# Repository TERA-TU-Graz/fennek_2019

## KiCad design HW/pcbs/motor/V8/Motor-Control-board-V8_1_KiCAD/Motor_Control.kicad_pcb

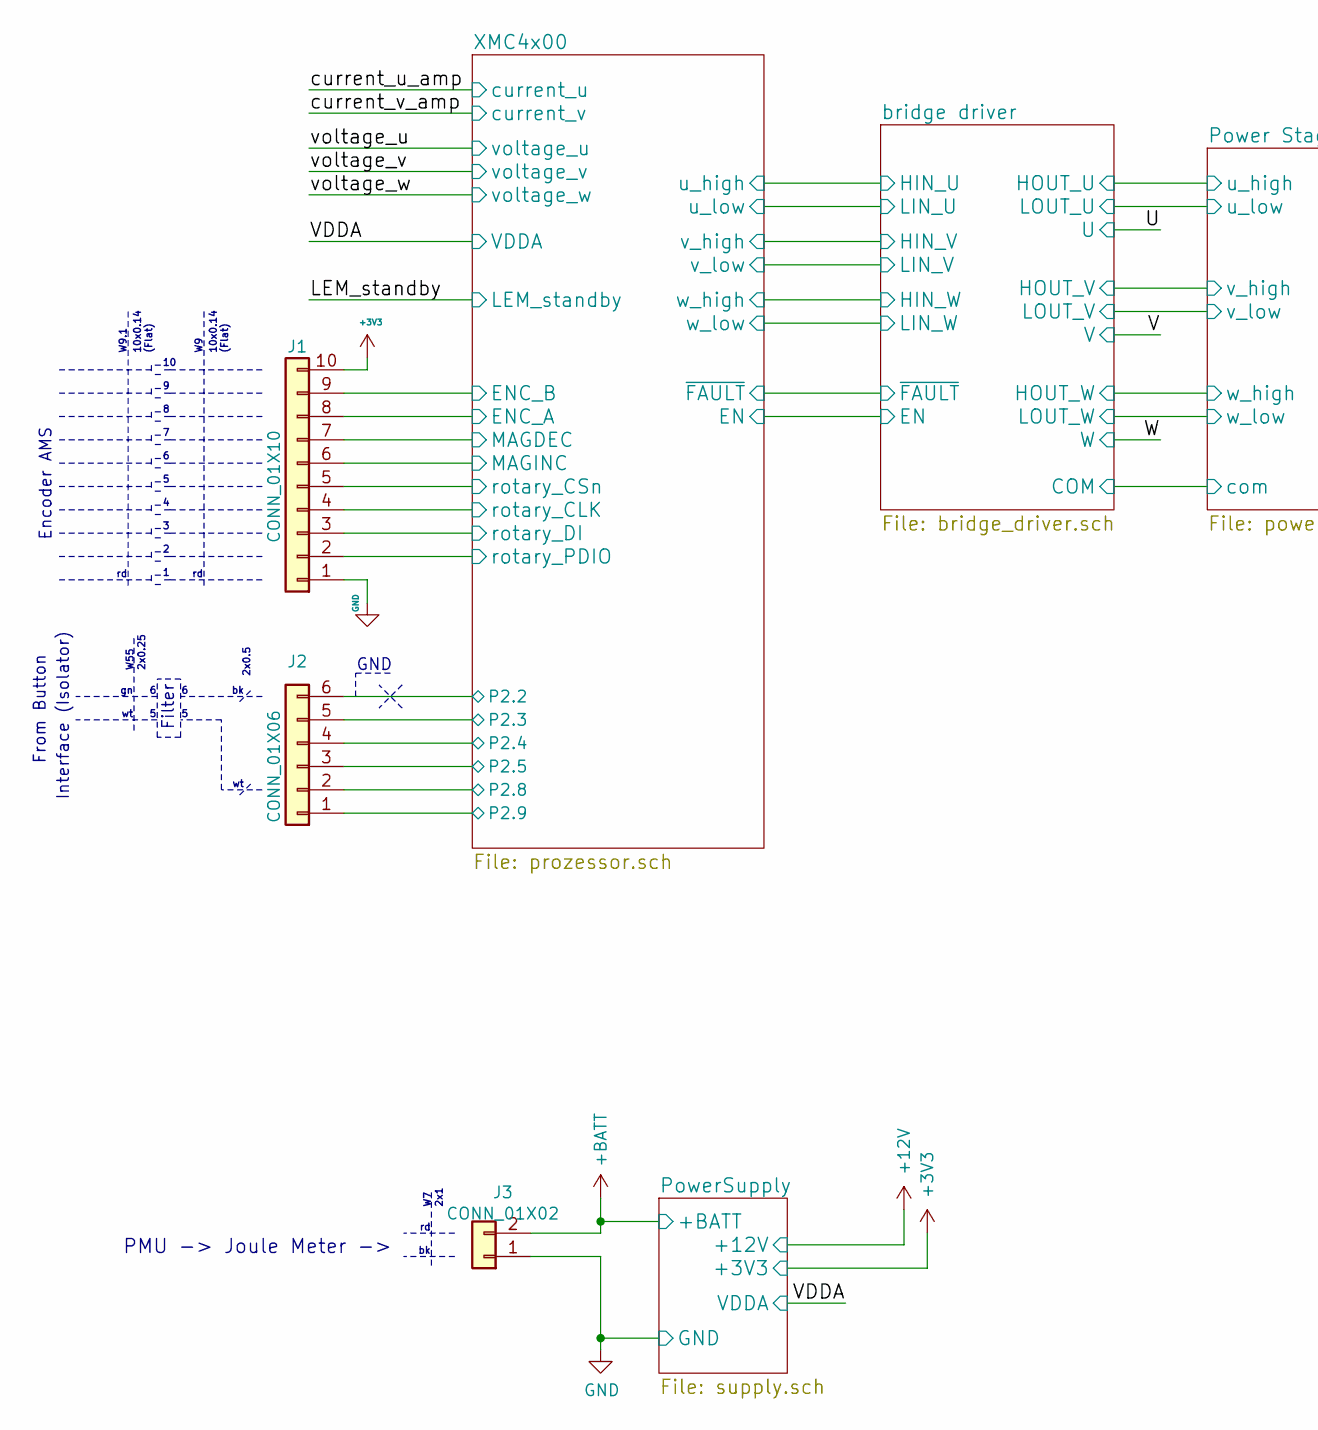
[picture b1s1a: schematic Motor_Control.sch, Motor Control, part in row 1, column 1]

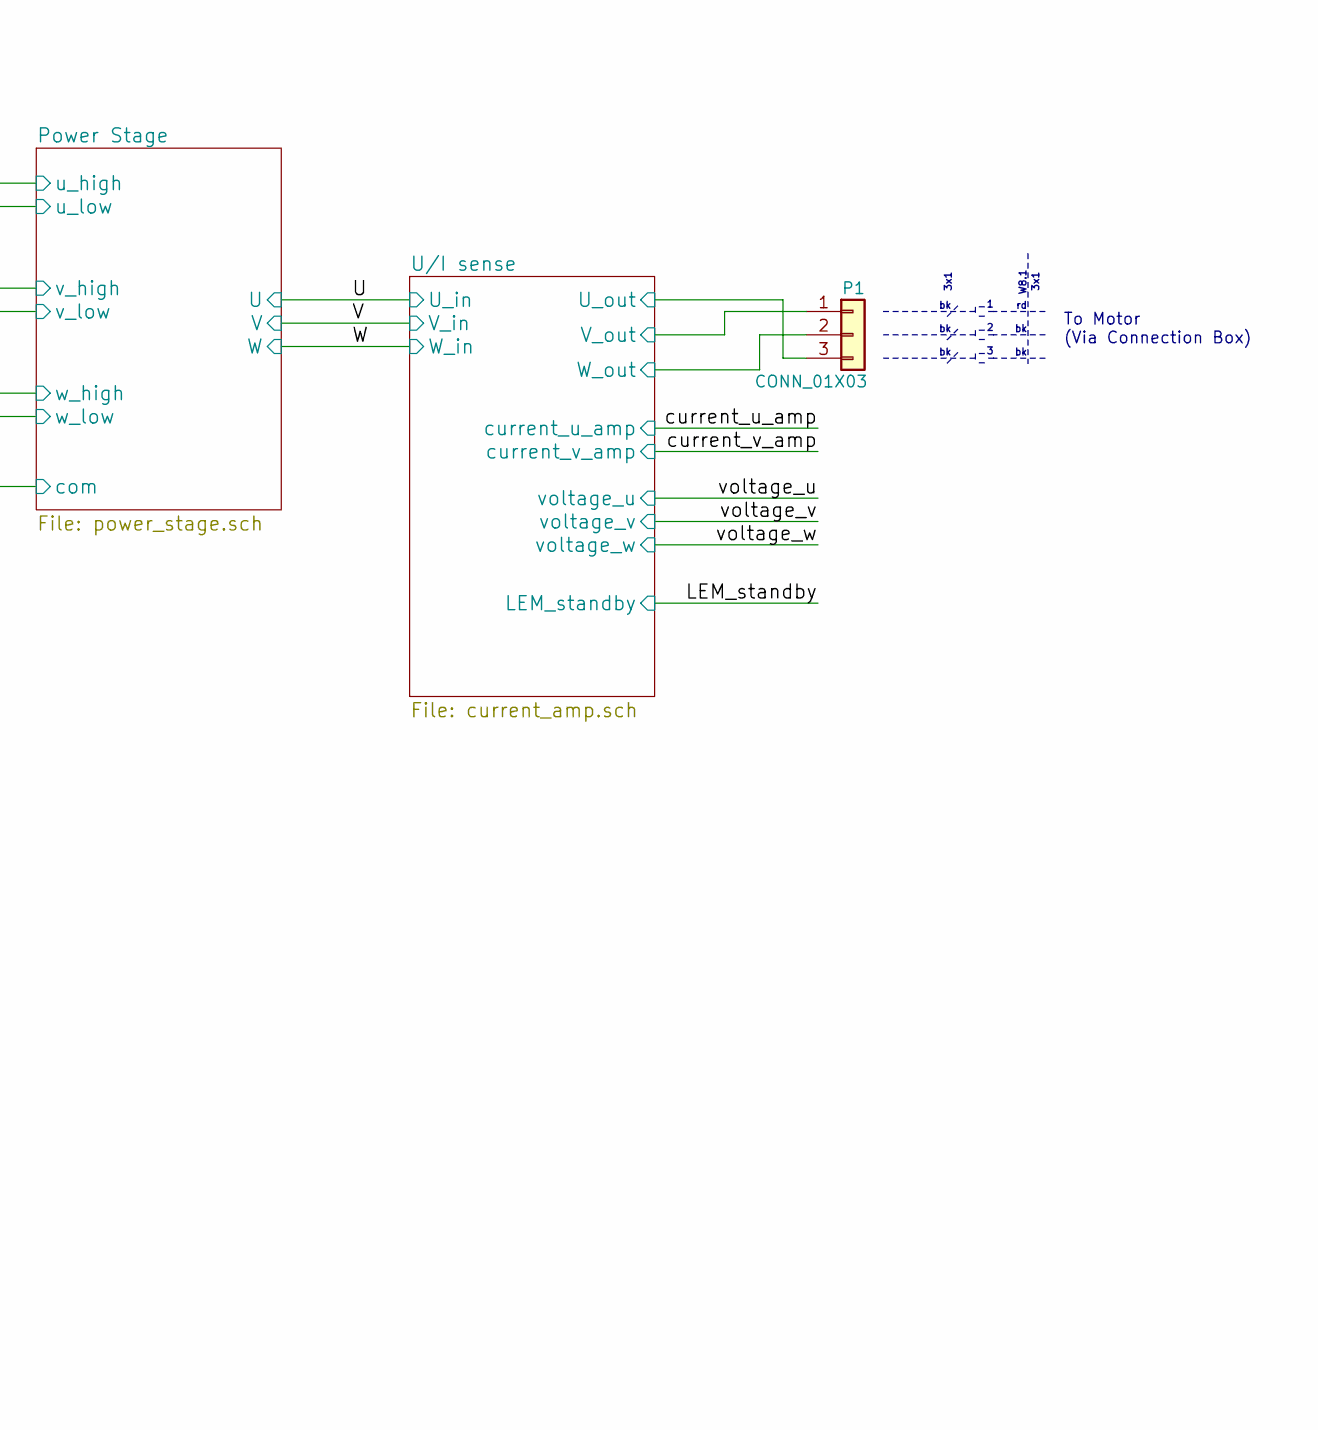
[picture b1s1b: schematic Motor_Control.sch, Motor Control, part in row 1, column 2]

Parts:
J1: CONN_01X10; Molex_PicoBlade_53398-1071_10x1.25mm_Straight
J2: CONN_01X06; Pin_Header_Straight_1x06_Pitch2.54mm
J3: CONN_01X02; PhoenixContact_MSTB-GF_02x5.08mm_Angled_ThreadedFlange
P1: CONN_01X03; PhoenixContact_MSTBA-G_03x5.08mm_Angled

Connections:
+3V3: J1.10; also elsewhere on the board
+BATT: J3.2; also elsewhere on the board
<root sheet>ENC_A: J1.8; also elsewhere on the board
<root sheet>ENC_B: J1.9; also elsewhere on the board
<root sheet>MAGDEC: J1.7; also elsewhere on the board
<root sheet>MAGINC: J1.6; also elsewhere on the board
<root sheet>U_out: P1.3; also elsewhere on the board
<root sheet>V_out: P1.1; also elsewhere on the board
<root sheet>W_out: P1.2; also elsewhere on the board
<root sheet>rotary_CLK: J1.4; also elsewhere on the board
<root sheet>rotary_CSn: J1.5; also elsewhere on the board
<root sheet>rotary_DI: J1.3; also elsewhere on the board
<root sheet>rotary_PDIO: J1.2; also elsewhere on the board
GND: J1.1, J3.1; also elsewhere on the board
unnamed 58: J2.1; also elsewhere on the board
unnamed 59: J2.2; also elsewhere on the board
unnamed 60: J2.3; also elsewhere on the board
unnamed 61: J2.4; also elsewhere on the board
unnamed 62: J2.5; also elsewhere on the board
unnamed 63: J2.6; also elsewhere on the board

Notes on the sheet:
10x0.14 (Flat)
W9.1
Encoder AMS
3x1
W8.1
To Motor (Via Connection Box)
PMU -> Joule Meter ->
2x1
GND
2x0.5
Filter
From Button
Interface (Isolator)
2x0.25
W55

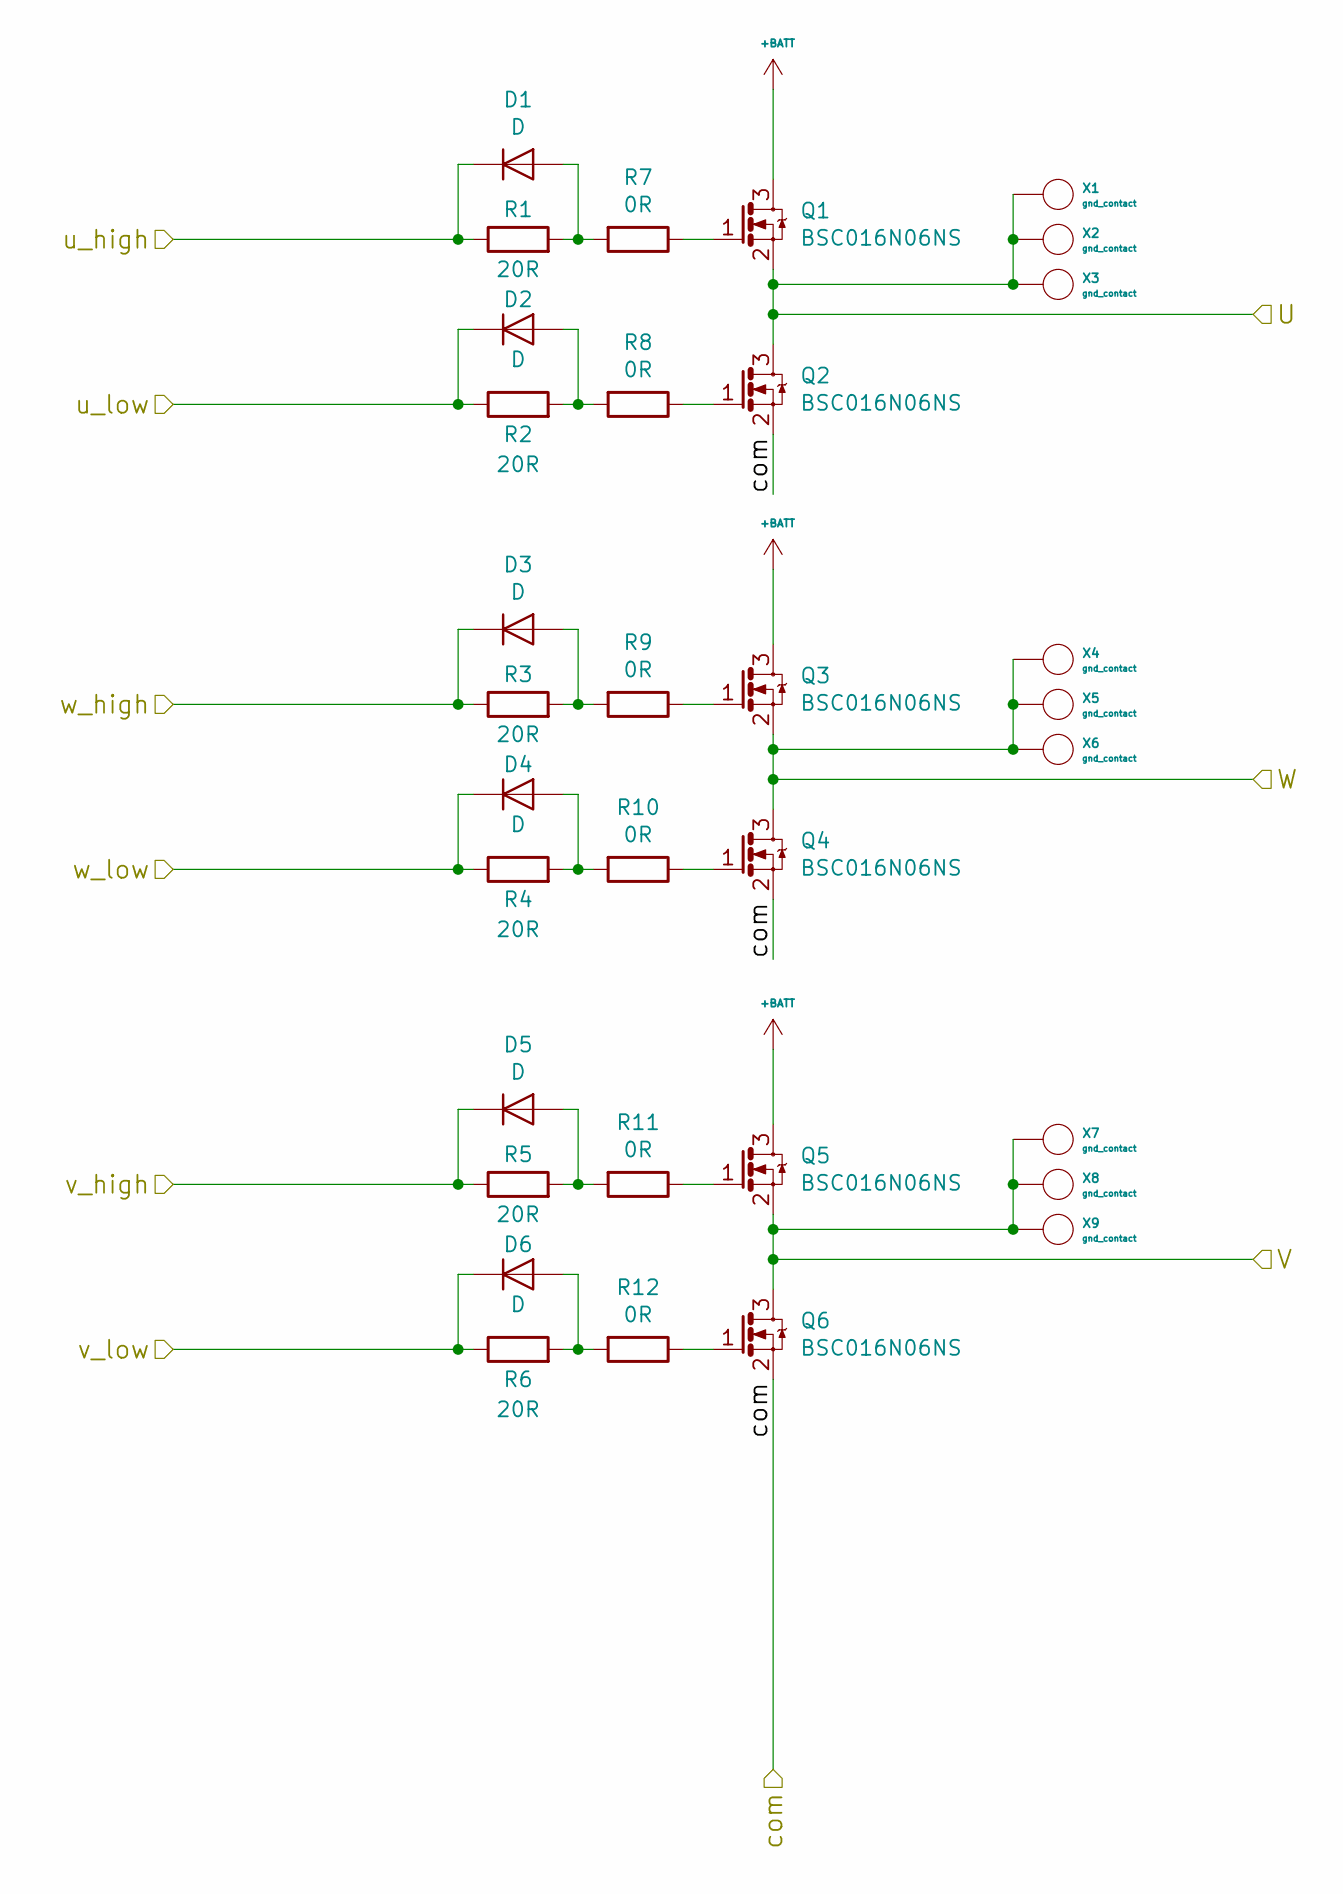
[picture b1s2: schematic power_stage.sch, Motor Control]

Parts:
D1, D2, D3, D4, D5, D6: D; SOD-323
Q1, Q2, Q3, Q4, Q5, Q6: BSC016N06NS; INF-PG-TDSON-8
R1, R2, R3, R4, R5, R6: 20R; R_0603in
R7, R8, R9, R10, R11, R12: 0R; R_0603in
X1, X2, X3, X4, X5, X6, X7, X8, X9: gnd_contact; via_0.4mm

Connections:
+BATT: Q1.3 (D), Q3.3 (D), Q5.3 (D); also elsewhere on the board
<root sheet>COM: Q2.2 (S), Q4.2 (S), Q6.2 (S); also elsewhere on the board
<root sheet>HOUT_V: D5.1 (K), R5.1; also elsewhere on the board
<root sheet>LOUT_V: D6.1 (K), R6.1; also elsewhere on the board
<root sheet>U: Q1.2 (S), Q2.3 (D), X1.1, X2.1, X3.1; also elsewhere on the board
<root sheet>V: Q5.2 (S), Q6.3 (D), X7.1, X8.1, X9.1; also elsewhere on the board
<root sheet>W_out: Q3.2 (S), Q4.3 (D), X4.1, X5.1, X6.1; also elsewhere on the board
<root sheet>u_high: D1.1 (K), R1.1; also elsewhere on the board
<root sheet>u_low: D2.1 (K), R2.1; also elsewhere on the board
<root sheet>w_high: D3.1 (K), R3.1; also elsewhere on the board
<root sheet>w_low: D4.1 (K), R4.1; also elsewhere on the board
unnamed: D1.2 (A), R1.2, R7.2
unnamed: D2.2 (A), R2.2, R8.2
unnamed: D3.2 (A), R3.2, R9.2
unnamed: D4.2 (A), R4.2, R10.2
unnamed: D5.2 (A), R5.2, R11.2
unnamed: D6.2 (A), R6.2, R12.2
unnamed: Q1.1 (G), R7.1
unnamed: Q2.1 (G), R8.1
unnamed: Q3.1 (G), R9.1
unnamed: Q4.1 (G), R10.1
unnamed: Q5.1 (G), R11.1
unnamed: Q6.1 (G), R12.1

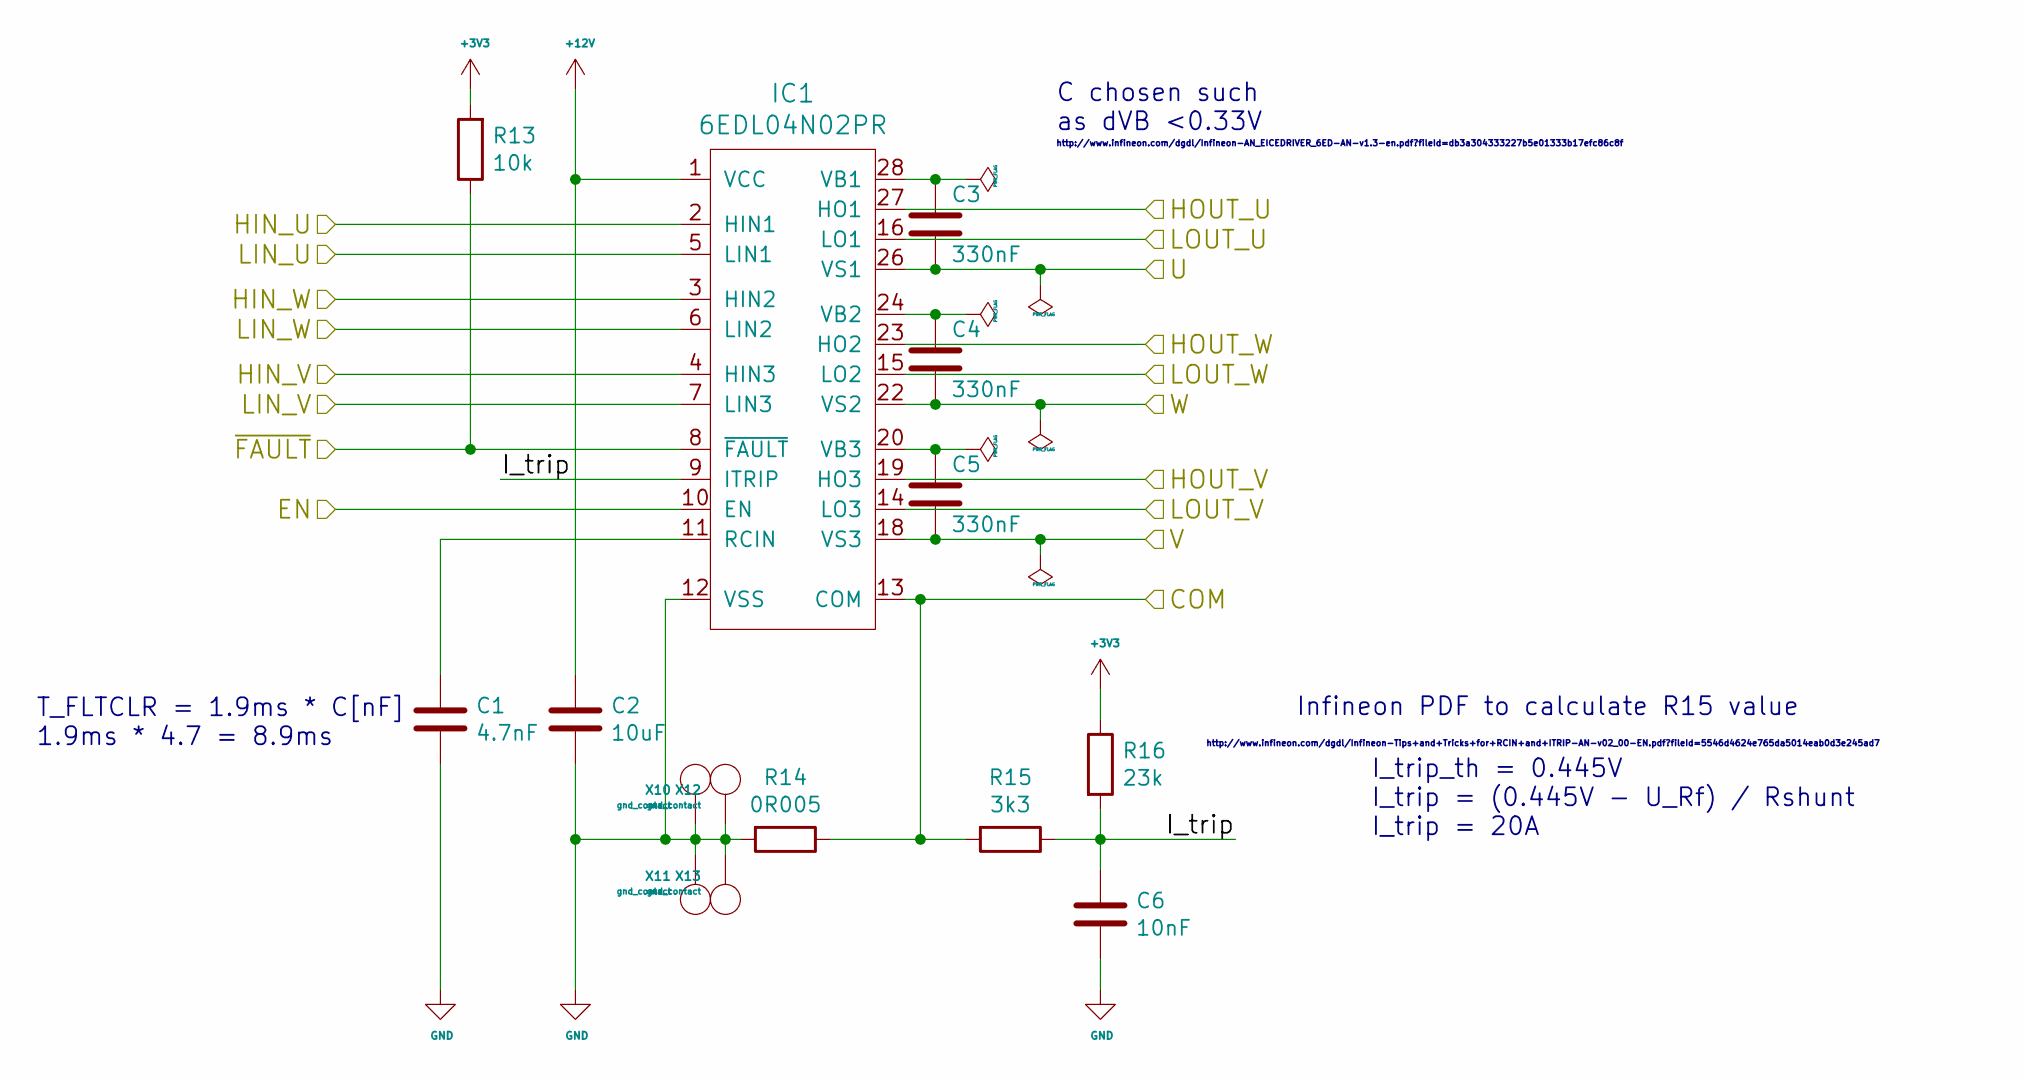
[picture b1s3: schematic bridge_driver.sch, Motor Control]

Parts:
C1: 4.7nF; C_0603in
C2: 10uF; C_0603in
C3, C4, C5: 330nF; C_0603in
C6: 10nF; C_0603in
IC1: 6EDL04N02PR
R13: 10k; R_0603in
R14: 0R005; R_2512in
R15: 3k3; R_0603in
R16: 23k; R_0603in
X10, X11, X12, X13: gnd_contact; via_0.4mm

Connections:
+3V3: R13.2, R16.1; also elsewhere on the board
+12V: C2.1, IC1.1 (VCC); also elsewhere on the board
/bridge driver/I_trip: C6.1, IC1.9 (ITRIP), R15.1, R16.2
<root sheet>COM: IC1.13 (COM), R14.1, R15.2; also elsewhere on the board
<root sheet>EN: IC1.10 (EN); also elsewhere on the board
<root sheet>HOUT_V: IC1.19 (HO3); also elsewhere on the board
<root sheet>LOUT_V: IC1.14 (LO3); also elsewhere on the board
<root sheet>U: C3.2, IC1.26 (VS1); also elsewhere on the board
<root sheet>V: C5.2, IC1.18 (VS3); also elsewhere on the board
<root sheet>W_out: C4.2, IC1.22 (VS2); also elsewhere on the board
<root sheet>u_high: IC1.27 (HO1); also elsewhere on the board
<root sheet>u_high_1: IC1.2 (HIN1); also elsewhere on the board
<root sheet>u_low: IC1.16 (LO1); also elsewhere on the board
<root sheet>u_low_1: IC1.5 (LIN1); also elsewhere on the board
<root sheet>v_high: IC1.4 (HIN3); also elsewhere on the board
<root sheet>v_low: IC1.7 (LIN3); also elsewhere on the board
<root sheet>w_high: IC1.23 (HO2); also elsewhere on the board
<root sheet>w_high_1: IC1.3 (HIN2); also elsewhere on the board
<root sheet>w_low: IC1.15 (LO2); also elsewhere on the board
<root sheet>w_low_1: IC1.6 (LIN2); also elsewhere on the board
<root sheet>~FAULT: IC1.8 (~FAULT), R13.1; also elsewhere on the board
GND: C1.2, C2.2, C6.2, IC1.12 (VSS), R14.2, X10.1, X11.1, X12.1, X13.1; also elsewhere on the board
unnamed: C1.1, IC1.11 (RCIN)
unnamed: C3.1, IC1.28 (VB1)
unnamed: C4.1, IC1.24 (VB2)
unnamed: C5.1, IC1.20 (VB3)

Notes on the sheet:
http://www.infineon.com/dgdl/Infineon-Tips+and+Tricks+for+RCIN+and+ITRIP-AN-v02_00-EN.pdf?fileId=5546d4624e765da5014eab0d3e245ad7
Infineon PDF to calculate R15 value
T_FLTCLR = 1.9ms * C[nF] 1.9ms * 4.7 = 8.9ms
C chosen such as dVB <0.33V
I_trip_th = 0.445V I_trip = (0.445V - U_Rf) / Rshunt I_trip = 20A
http://www.infineon.com/dgdl/Infineon-AN_EICEDRIVER_6ED-AN-v1.3-en.pdf?fileId=db3a304333227b5e01333b17efc86c8f

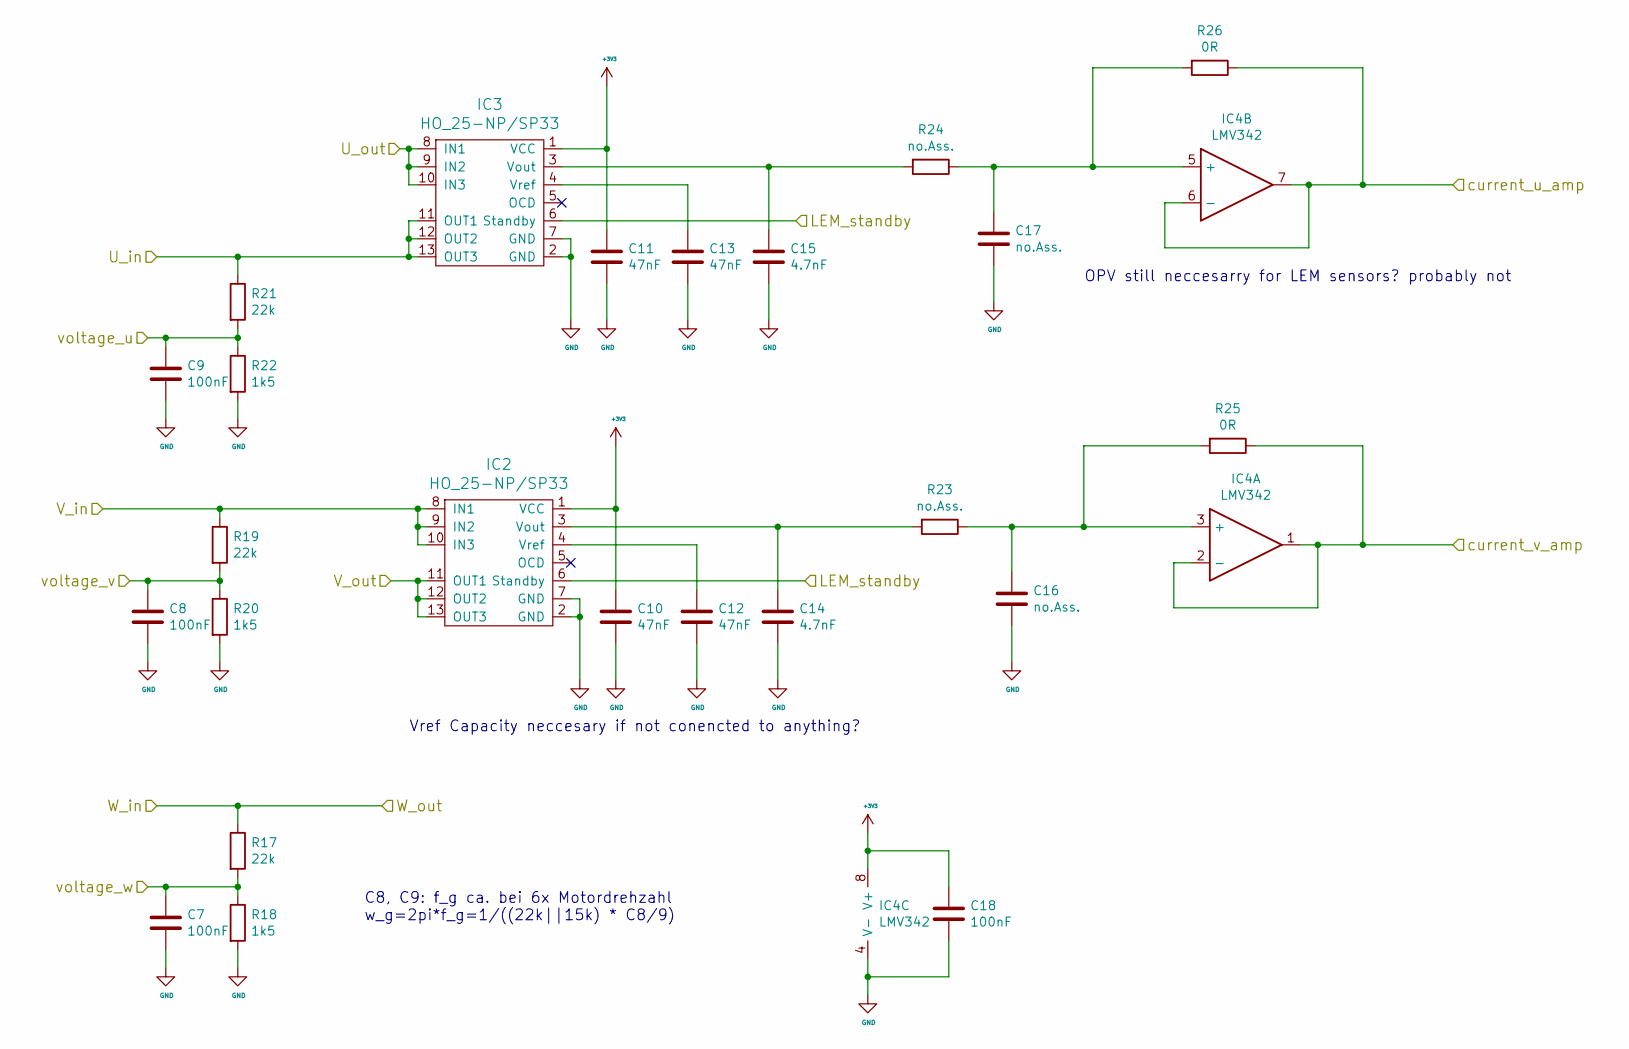
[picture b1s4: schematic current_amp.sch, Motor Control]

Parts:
C7, C8, C9, C18: 100nF; C_0603in
C10, C11, C12, C13: 47nF; C_0603in
C14, C15: 4.7nF; C_0603in
C16, C17: no.Ass.; C_0603in
IC2, IC3: HO_25-NP/SP33; HO_25-NP_SP33
IC4: LMV342
R17, R19, R21: 22k; R_0603in
R18, R20, R22: 1k5; R_0603in
R23, R24: no.Ass.; R_0603in
R25, R26: 0R; R_0603in

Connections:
+3V3: C10.1, C11.1, C18.1, IC2.1 (VCC), IC3.1 (VCC), IC4.8 (V+); also elsewhere on the board
<root sheet>LEM_standby: IC2.6 (Standby), IC3.6 (Standby); also elsewhere on the board
<root sheet>U: IC3.11 (OUT1), IC3.12 (OUT2), IC3.13 (OUT3), R21.1; also elsewhere on the board
<root sheet>U_out: IC3.8 (IN1), IC3.9 (IN2), IC3.10 (IN3); also elsewhere on the board
<root sheet>V: IC2.8 (IN1), IC2.9 (IN2), IC2.10 (IN3), R19.1; also elsewhere on the board
<root sheet>V_out: IC2.11 (OUT1), IC2.12 (OUT2), IC2.13 (OUT3); also elsewhere on the board
<root sheet>W_out: R17.1; also elsewhere on the board
<root sheet>current_u_amp: IC4.6 (-), IC4.7, R26.1; also elsewhere on the board
<root sheet>current_v_amp: IC4.1, IC4.2 (-), R25.1; also elsewhere on the board
<root sheet>voltage_u: C9.1, R21.2, R22.1; also elsewhere on the board
<root sheet>voltage_v: C8.1, R19.2, R20.1; also elsewhere on the board
<root sheet>voltage_w: C7.1, R17.2, R18.1; also elsewhere on the board
GND: C7.2, C8.2, C9.2, C10.2, C11.2, C12.2, C13.2, C14.2, C15.2, C16.2, C17.2, C18.2, IC2.2 (GND), IC2.7 (GND), IC3.2 (GND), IC3.7 (GND), IC4.4 (V-), R18.2, R20.2, R22.2; also elsewhere on the board
unnamed: C12.1, IC2.4 (Vref)
unnamed: C13.1, IC3.4 (Vref)
unnamed: C14.1, IC2.3 (Vout), R23.2
unnamed: C15.1, IC3.3 (Vout), R24.2
unnamed: C16.1, IC4.3 (+), R23.1, R25.2
unnamed: C17.1, IC4.5 (+), R24.1, R26.2

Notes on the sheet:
OPV still neccesarry for LEM sensors? probably not
Vref Capacity neccesary if not conencted to anything?
C8, C9: f_g ca. bei 6x Motordrehzahl w_g=2pi*f_g=1/((22k||15k) * C8/9)

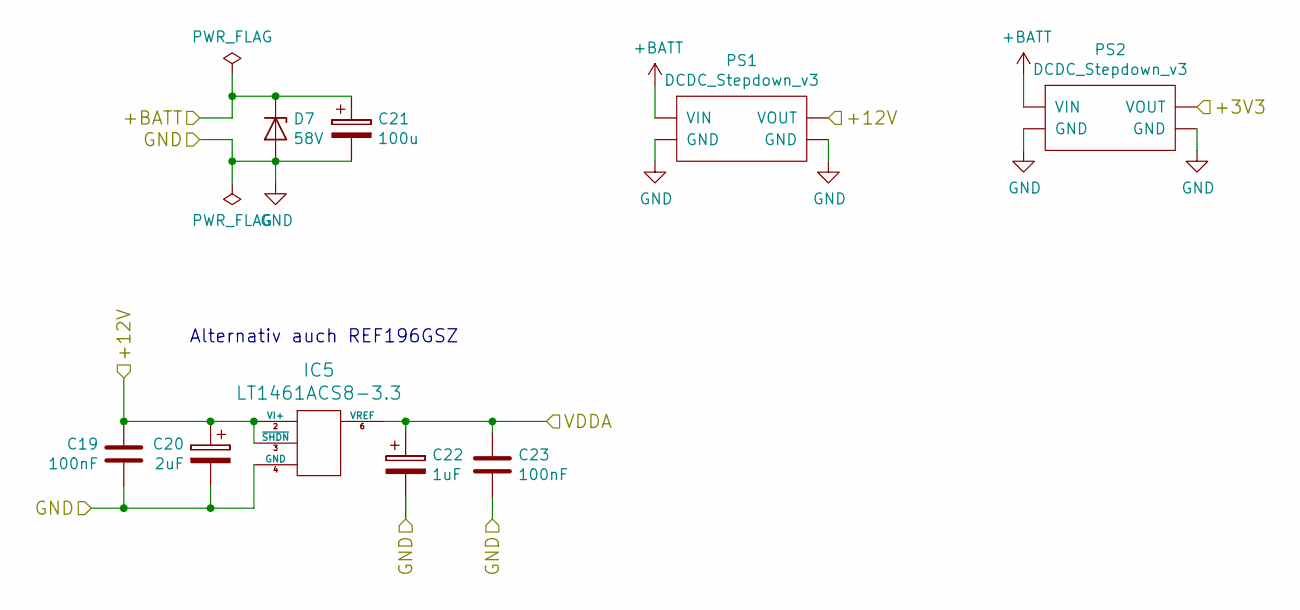
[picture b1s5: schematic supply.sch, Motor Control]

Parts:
C19, C23: 100nF; C_0603in
C20: 2uF; C_0603in
C21: 100u; ElkoC-12.5x20mm
C22: 1uF; C_0603in
D7: 58V; DO-214AA
IC5: LT1461ACS8-3.3; LT1461ACS8
PS1, PS2: DCDC_Stepdown_v3

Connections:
+3V3: PS2.2 (VOUT); also elsewhere on the board
+12V: C19.1, C20.1, IC5.2 (VI+), IC5.3 (~SHDN), PS1.2 (VOUT); also elsewhere on the board
+BATT: C21.1, D7.1 (K), PS1.1 (VIN), PS2.1 (VIN); also elsewhere on the board
<root sheet>VDDA: C22.1, C23.1, IC5.6 (VREF); also elsewhere on the board
GND: C19.2, C20.2, C21.2, C22.2, C23.2, D7.2 (A), IC5.4 (GND), PS1.3 (GND), PS1.4 (GND), PS2.3 (GND), PS2.4 (GND); also elsewhere on the board

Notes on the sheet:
Alternativ auch REF196GSZ

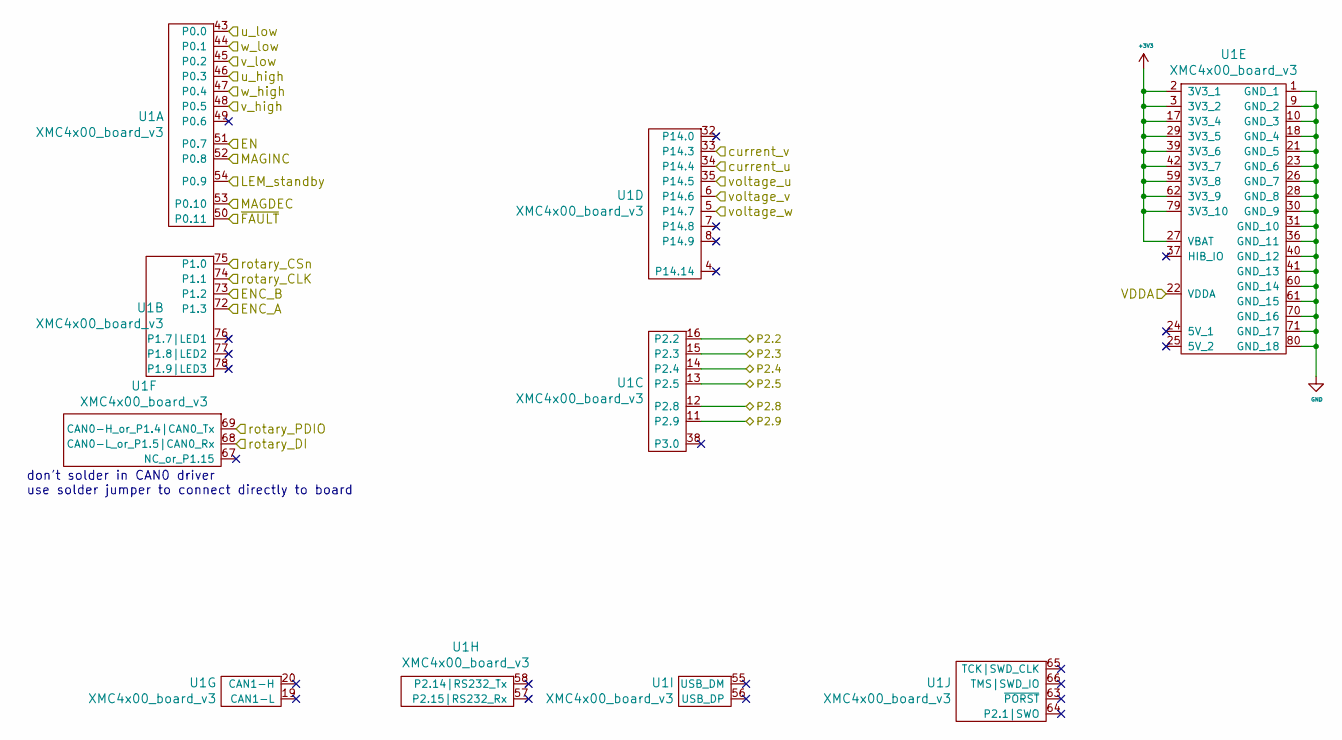
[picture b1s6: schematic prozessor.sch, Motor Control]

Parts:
U1: XMC4x00_board_v3; XMC4x00-board_v3-0

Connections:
+3V3: U1.2 (3V3_1), U1.3 (3V3_2), U1.17 (3V3_4), U1.27 (VBAT), U1.29 (3V3_5), U1.39 (3V3_6), U1.42 (3V3_7), U1.59 (3V3_8), U1.62 (3V3_9), U1.79 (3V3_10); also elsewhere on the board
<root sheet>EN: U1.51 (P0.7); also elsewhere on the board
<root sheet>ENC_A: U1.72 (P1.3); also elsewhere on the board
<root sheet>ENC_B: U1.73 (P1.2); also elsewhere on the board
<root sheet>LEM_standby: U1.54 (P0.9); also elsewhere on the board
<root sheet>MAGDEC: U1.53 (P0.10); also elsewhere on the board
<root sheet>MAGINC: U1.52 (P0.8); also elsewhere on the board
<root sheet>VDDA: U1.22 (VDDA); also elsewhere on the board
<root sheet>current_u_amp: U1.34 (P14.4); also elsewhere on the board
<root sheet>current_v_amp: U1.33 (P14.3); also elsewhere on the board
<root sheet>rotary_CLK: U1.74 (P1.1); also elsewhere on the board
<root sheet>rotary_CSn: U1.75 (P1.0); also elsewhere on the board
<root sheet>rotary_DI: U1.68 (CAN0-L_or_P1.5|CAN0_Rx); also elsewhere on the board
<root sheet>rotary_PDIO: U1.69 (CAN0-H_or_P1.4|CAN0_Tx); also elsewhere on the board
<root sheet>u_high_1: U1.46 (P0.3); also elsewhere on the board
<root sheet>u_low_1: U1.43 (P0.0); also elsewhere on the board
<root sheet>v_high: U1.48 (P0.5); also elsewhere on the board
<root sheet>v_low: U1.45 (P0.2); also elsewhere on the board
<root sheet>voltage_u: U1.35 (P14.5); also elsewhere on the board
<root sheet>voltage_v: U1.6 (P14.6); also elsewhere on the board
<root sheet>voltage_w: U1.5 (P14.7); also elsewhere on the board
<root sheet>w_high_1: U1.47 (P0.4); also elsewhere on the board
<root sheet>w_low_1: U1.44 (P0.1); also elsewhere on the board
<root sheet>~FAULT: U1.50 (P0.11); also elsewhere on the board
GND: U1.1 (GND_1), U1.9 (GND_2), U1.10 (GND_3), U1.18 (GND_4), U1.21 (GND_5), U1.23 (GND_6), U1.26 (GND_7), U1.28 (GND_8), U1.30 (GND_9), U1.31 (GND_10), U1.36 (GND_11), U1.40 (GND_12), U1.41 (GND_13), U1.60 (GND_14), U1.61 (GND_15), U1.70 (GND_16), U1.71 (GND_17), U1.80 (GND_18); also elsewhere on the board
unnamed 58: U1.11 (P2.9); also elsewhere on the board
unnamed 59: U1.12 (P2.8); also elsewhere on the board
unnamed 60: U1.13 (P2.5); also elsewhere on the board
unnamed 61: U1.14 (P2.4); also elsewhere on the board
unnamed 62: U1.15 (P2.3); also elsewhere on the board
unnamed 63: U1.16 (P2.2); also elsewhere on the board

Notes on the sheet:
don't solder in CAN0 driver use solder jumper to connect directly to board

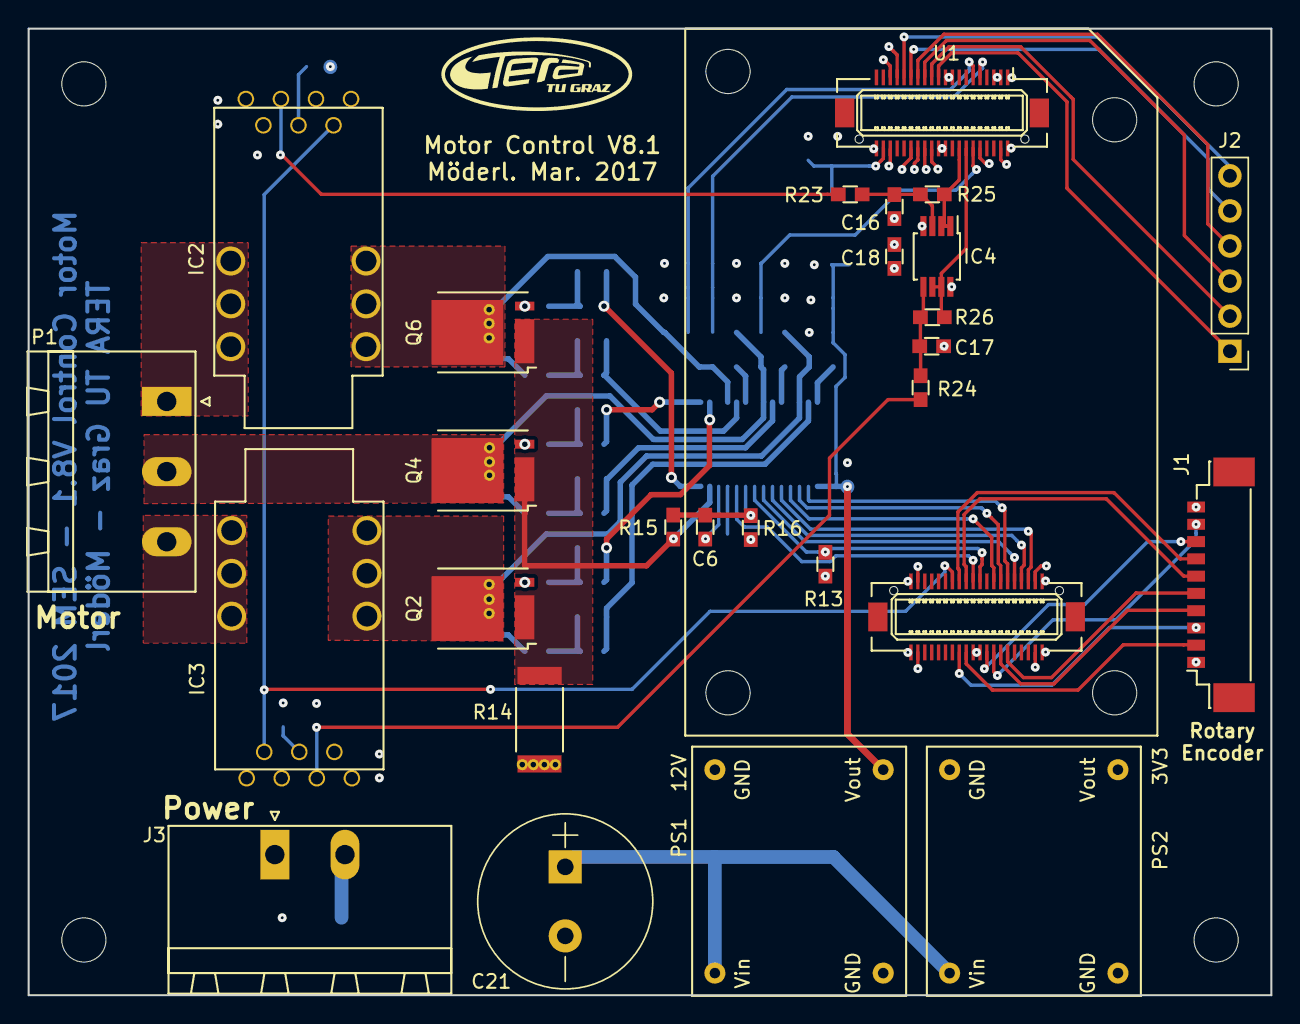
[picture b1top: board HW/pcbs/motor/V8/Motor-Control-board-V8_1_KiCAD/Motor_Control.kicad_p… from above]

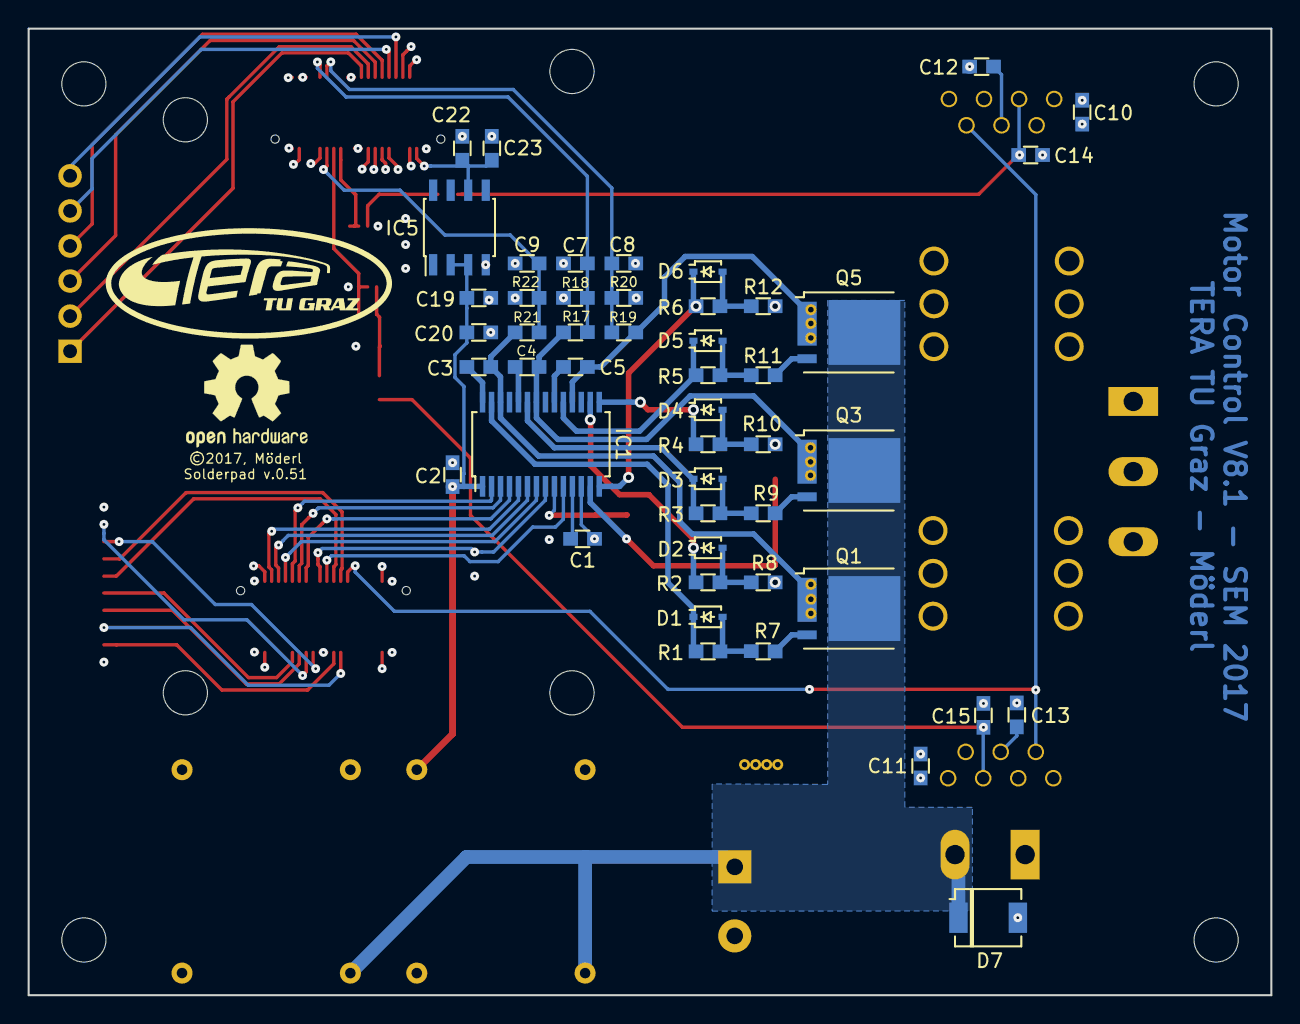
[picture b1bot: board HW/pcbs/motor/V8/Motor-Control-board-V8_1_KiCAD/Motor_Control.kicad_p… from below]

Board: 4 copper layers, 90.0 x 70.0 mm, 89 parts (56 on the bottom side), 68 nets.

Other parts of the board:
svg2mod: G***; TERA_Logo_SilkS_7.5x19mm
svg2mod#2: G***; TERA_Logo_SilkS_5x12.5mm

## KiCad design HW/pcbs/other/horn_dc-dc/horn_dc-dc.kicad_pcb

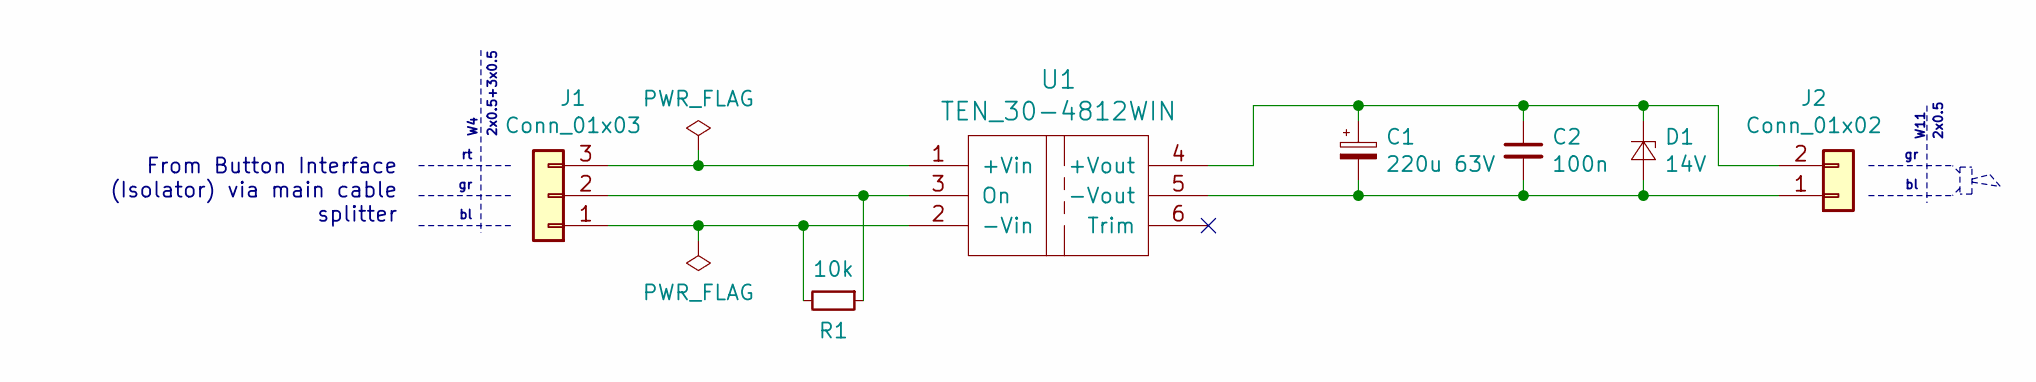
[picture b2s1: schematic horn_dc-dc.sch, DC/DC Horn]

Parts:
C1: 220u 63V; c_elec_10x10mm
C2: 100n; C_0603in
D1: 14V; SOD128
J1: Conn_01x03; JST_XH_B03B-XH-A_03x2.50mm_Straight
J2: Conn_01x02; JST_EH_B02B-EH-A_02x2.50mm_Straight
R1: 10k; R_0603in
U1: TEN_30-4812WIN; TEN_30-xxxx

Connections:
unnamed: C1.1, C2.1, D1.1 (K), J2.2, U1.4 (+Vout)
unnamed: C1.2, C2.2, D1.2 (A), J2.1, U1.5 (-Vout)
unnamed: J1.1, R1.2, U1.2 (-Vin)
unnamed: J1.2, R1.1, U1.3 (On)
unnamed: J1.3, U1.1 (+Vin)

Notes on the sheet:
2x0.5+3x0.5
From Button Interface (Isolator) via main cable splitter
2x0.5
W11

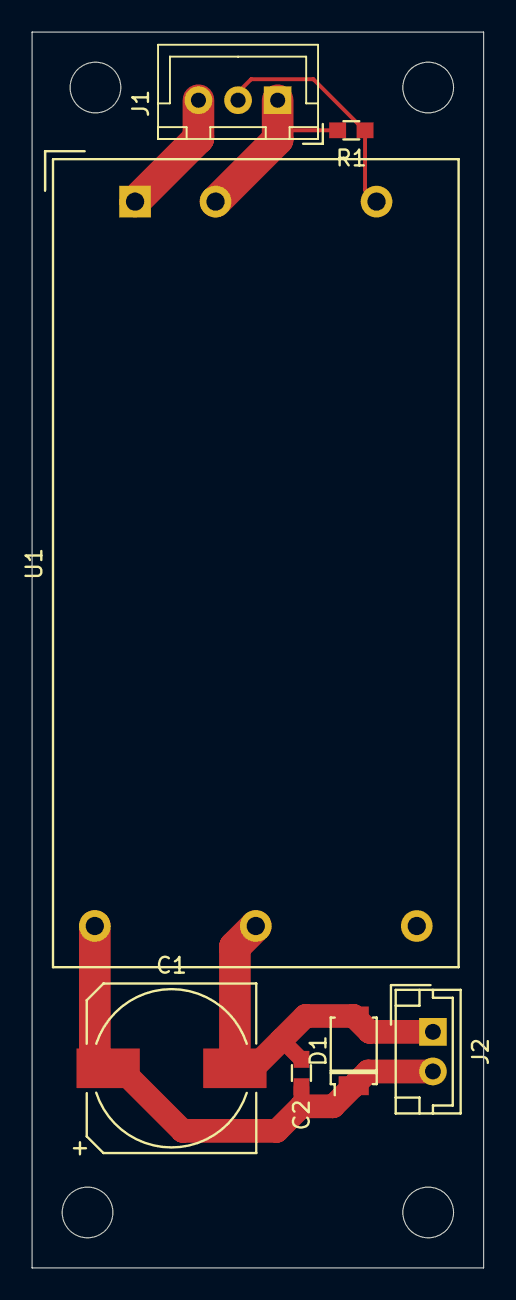
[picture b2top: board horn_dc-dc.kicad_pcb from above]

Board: 2 copper layers, 28.5 x 78.0 mm, 7 parts (0 on the bottom side), 5 nets.

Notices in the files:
HW/pcbs/BMS/Current_Sense/current_sense_v2_lem/current_sense.kicad_pcb:
©2017, Pöschl
HW/pcbs/BMS/master_fennek18/BMS_Master_V7 -- fennek18/BMS_Master_V7_kicad.kicad_pcb:
©Pöschl, 2018
©Pöschl, Apr. 2018
HW/pcbs/motor/V8/Motor-Control-board-V8_1_KiCAD/Motor_Control.kicad_pcb:
©2017, Möderl
